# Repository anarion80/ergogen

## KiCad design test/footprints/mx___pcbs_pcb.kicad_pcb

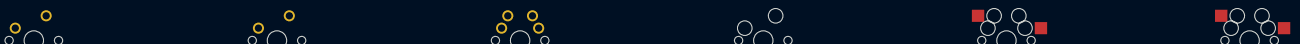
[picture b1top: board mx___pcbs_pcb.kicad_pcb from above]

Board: 2 copper layers, 6 parts (0 on the bottom side), 2 nets, no tracks yet.

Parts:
S1, S2, S3, S4, S5, S6: MX

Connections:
from: S1.1, S2.1, S3.1, S4.1, S5.1, S6.1
to: S1.2, S2.2, S3.2, S4.2, S5.2, S6.2
